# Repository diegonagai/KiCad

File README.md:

# KiCad
Este repositório contém os projetos de PCB desenvolvidos nos livros [KiCad 6 Like a Pro - Fundamentals and Projects](https://www.elektor.com/kicad-6-like-a-pro-fundamentals-and-projects) e [KiCad 6 Like A Pro – Projects, Tips and Recipes](https://www.elektor.com/kicad-6-like-a-pro-projects-tips-and-recipes) do Peter Dalmaris.

Estou usando a versão 7.0.7 do [KiCad EDA](https://www.kicad.org) para acompanhar os livros. As diferenças entre a versão 6 e a versão 7 do KiCad são muito pequenas, portanto é possível aproveitar todas as dicas dos livros!

Cada pasta deste repositório contém todo o projeto e um print frontal e traseiro da placa final.

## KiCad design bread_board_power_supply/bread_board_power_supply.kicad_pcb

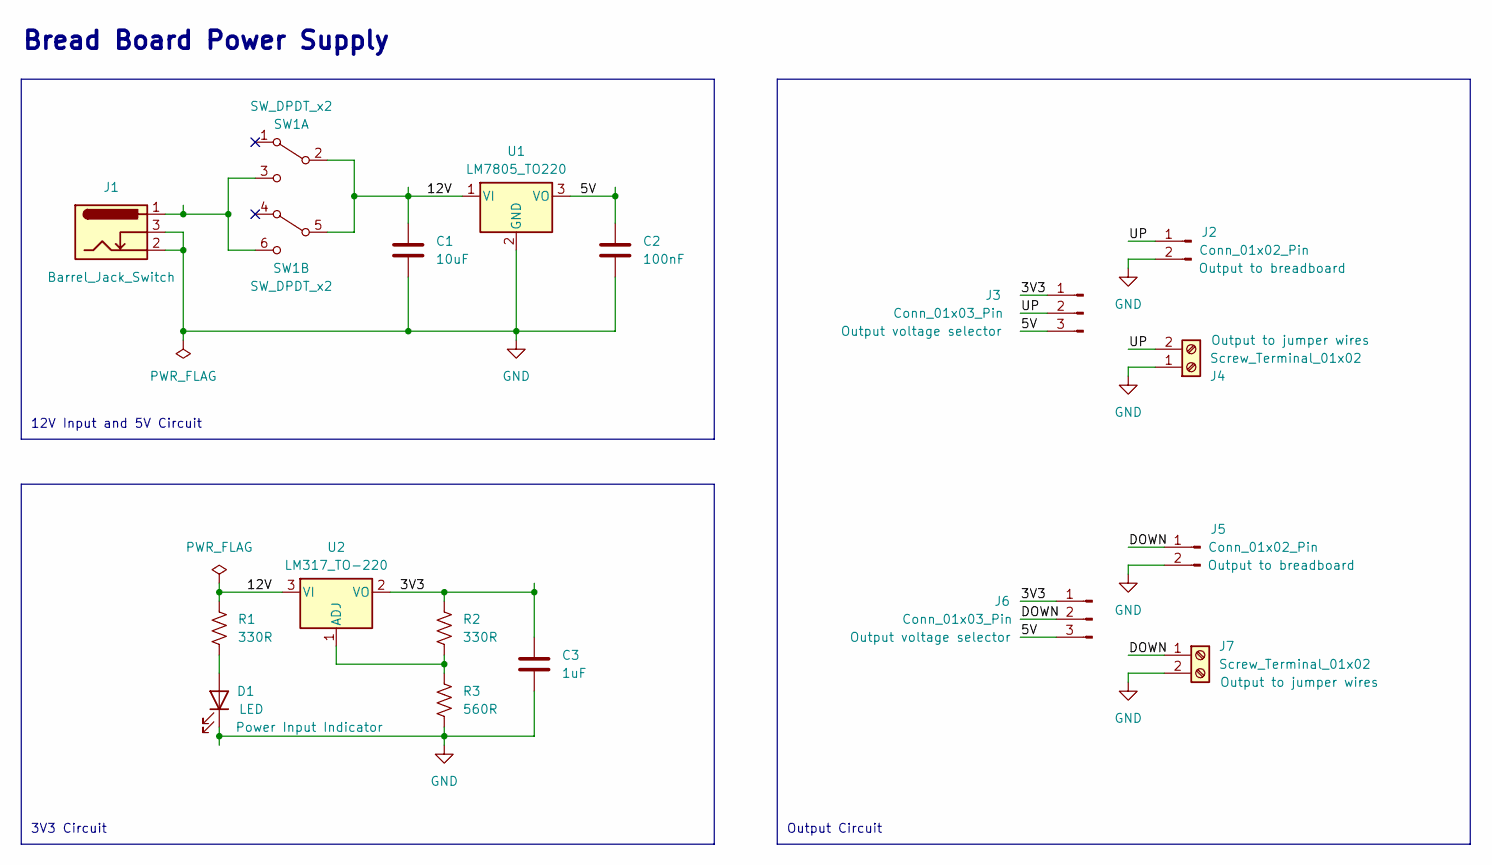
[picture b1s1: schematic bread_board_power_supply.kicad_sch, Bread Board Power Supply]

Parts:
C1: 10uF; C_Disc_D3.0mm_W1.6mm_P2.50mm
C2: 100nF; C_Disc_D3.0mm_W1.6mm_P2.50mm
C3: 1uF; C_Disc_D3.0mm_W1.6mm_P2.50mm
D1: LED; LED_D5.0mm
J1: Barrel_Jack_Switch; BarrelJack_Horizontal
J2, J5: Conn_01x02_Pin; PinHeader_1x02_P2.54mm_Vertical
J3, J6: Conn_01x03_Pin; PinHeader_1x03_P2.54mm_Vertical
J4, J7: Screw_Terminal_01x02; TerminalBlock_bornier-2_P5.08mm
R1, R2: 330R; R_Axial_DIN0204_L3.6mm_D1.6mm_P5.08mm_Horizontal
R3: 560R; R_Axial_DIN0204_L3.6mm_D1.6mm_P5.08mm_Horizontal
SW1: SW_DPDT_x2; SW_CuK_JS202011CQN_DPDT_Straight
U1: LM7805_TO220; TO-220-3_Vertical
U2: LM317_TO-220; TO-220-3_Vertical

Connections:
/3V3: C3.1, J3.1, J6.1, R2.1, U2.2 (VO)
/5V: C2.1, J3.3, J6.3, U1.3 (VO)
/12V: C1.1, R1.1, SW1.2 (B), SW1.5 (B), U1.1 (VI), U2.3 (VI)
/DOWN: J5.1, J6.2, J7.1
/UP: J2.1, J3.2, J4.2
GND: C1.2, C2.2, C3.2, D1.1 (K), J1.2, J1.3, J2.2, J4.1, J5.2, J7.2, R3.2, U1.2 (GND)
unnamed: D1.2 (A), R1.2
unnamed: J1.1, SW1.3 (C), SW1.6 (C)
unnamed: R2.2, R3.1, U2.1 (ADJ)

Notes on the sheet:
Bread Board Power Supply
3V3 Circuit
12V Input and 5V Circuit
Output Circuit

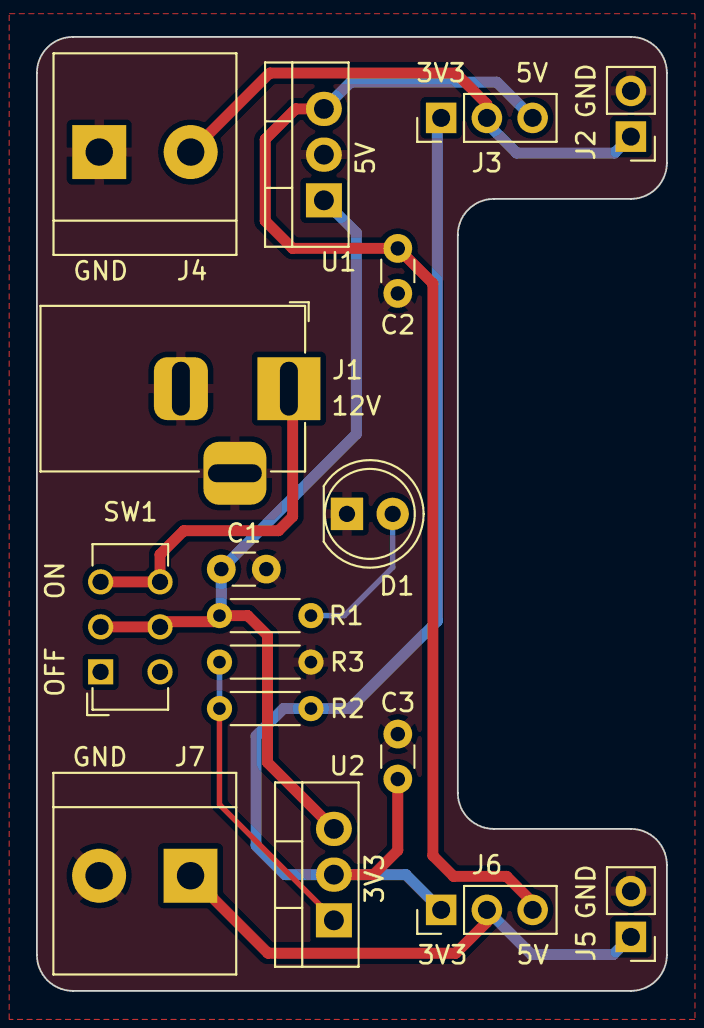
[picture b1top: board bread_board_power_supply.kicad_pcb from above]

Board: 2 copper layers, 35.0 x 53.0 mm, 18 parts (1 on the bottom side), 9 nets.

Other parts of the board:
TAG1: KiCad-Logo2_6mm_SilkScreen

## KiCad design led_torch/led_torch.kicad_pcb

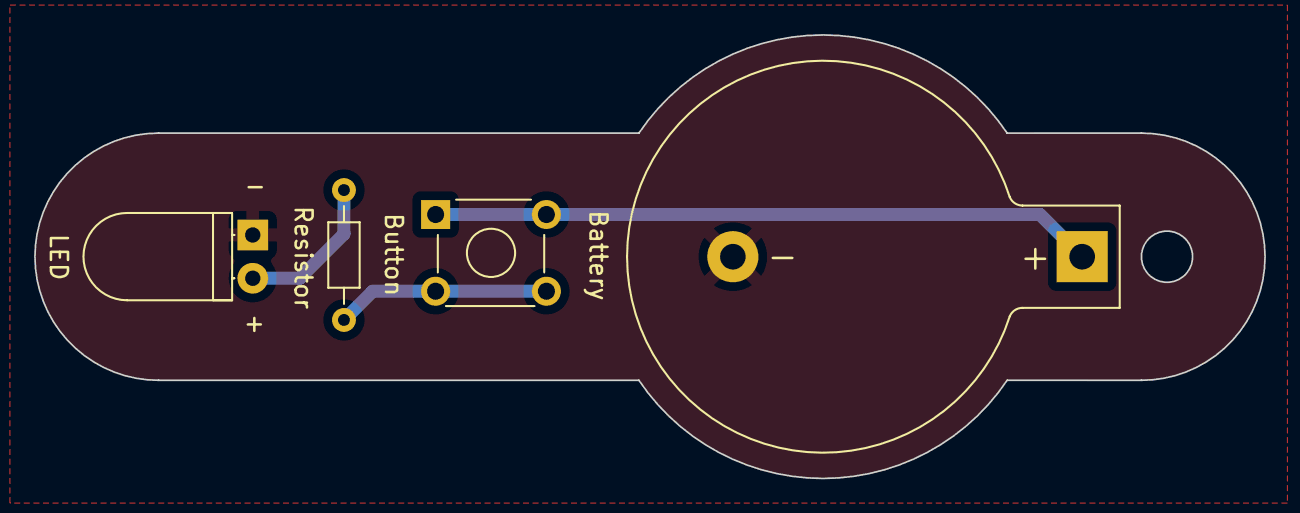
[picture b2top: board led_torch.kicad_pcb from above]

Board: 2 copper layers, 72.2 x 26.0 mm, 5 parts (1 on the bottom side), 4 nets.

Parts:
BT1: Battery; BatteryHolder_Keystone_103_1x20mm
D1: LED; LED_D5.0mm_Horizontal_O1.27mm_Z3.0mm_Clear
R1: Resistor; R_Axial_DIN0204_L3.6mm_D1.6mm_P7.62mm_Horizontal
SW1: Button; SW_TH_Tactile_Omron_B3F-10xx
TAG1: KiCad-Logo2_8mm_SilkScreen

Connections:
/ANODE: D1.2 (A), R1.2
/GND: BT1.2 (-), D1.1 (K)
/SW: R1.1, SW1.2
/VCC: BT1.1 (+), SW1.1

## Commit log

2023-12-09 Update LICENSE
